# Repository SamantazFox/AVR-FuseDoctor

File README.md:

AVR FuseDoctor
==============

Fuse doctor for AVR-based devices.

Enhanced version froked from https://github.com/nagaokashi/ATTiny_FuseDoctor,
that adds support for ATmegas and ATtiny2313(a)/4313.

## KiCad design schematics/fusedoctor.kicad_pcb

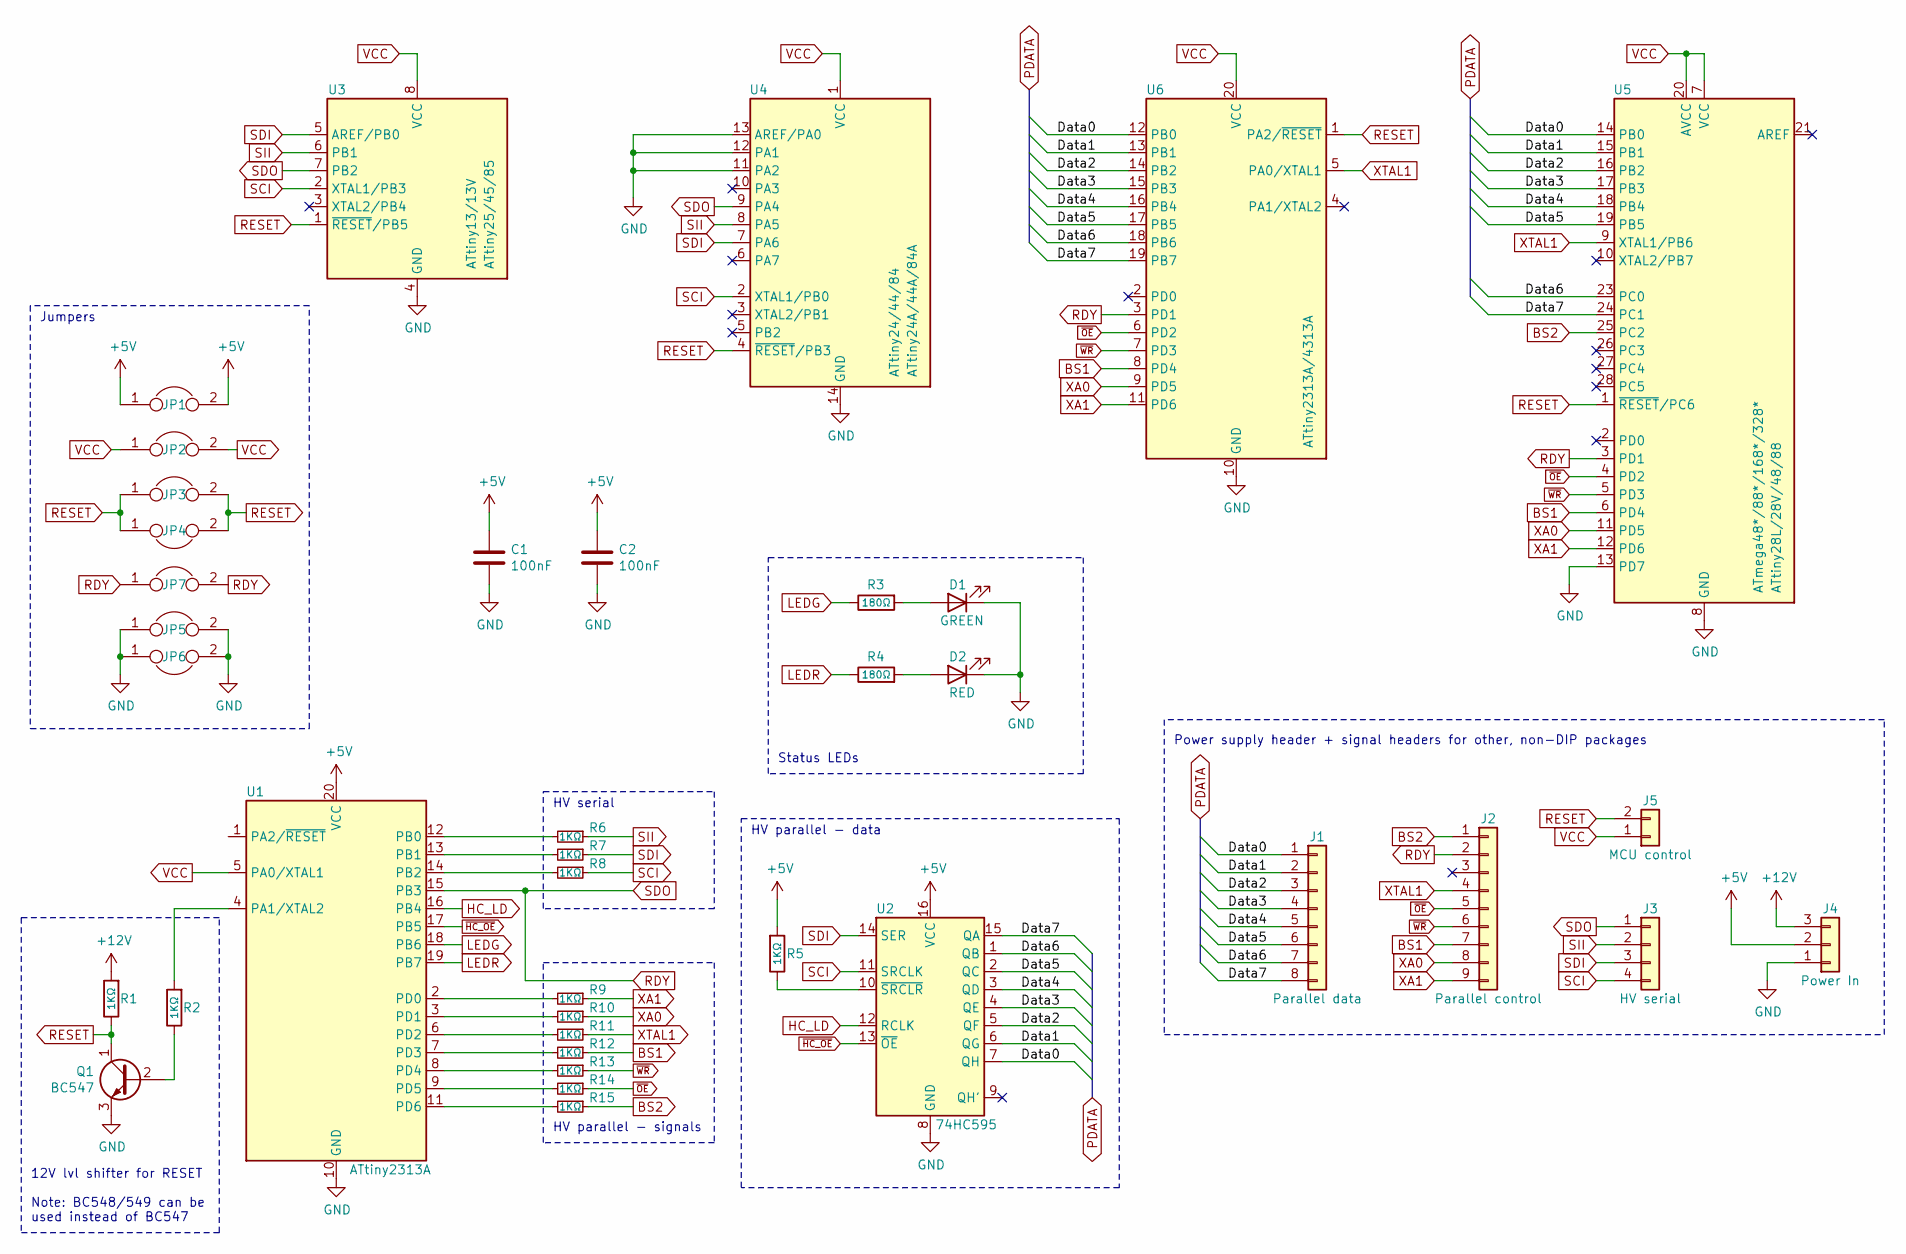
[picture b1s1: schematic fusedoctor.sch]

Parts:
C1, C2: 100nF; C_Axial_L3.8mm_D2.6mm_P7.50mm_Horizontal
D1: GREEN; LED_D3.0mm
D2: RED; LED_D3.0mm
J1: Parallel data; PinHeader_1x08_P2.54mm_Vertical
J2: Parallel control; PinHeader_1x09_P2.54mm_Vertical
J3: HV serial; PinHeader_1x04_P2.54mm_Vertical
J4: Power In; PinHeader_1x03_P2.54mm_Vertical
J5: MCU control; PinHeader_1x02_P2.54mm_Vertical
JP1, JP3, JP4: Jumper; R_Axial_DIN0207_L6.3mm_D2.5mm_P10.16mm_Horizontal
JP2: Jumper; R_Axial_DIN0207_L6.3mm_D2.5mm_P15.24mm_Horizontal
JP5, JP6, JP7: Jumper; R_Axial_DIN0207_L6.3mm_D2.5mm_P7.62mm_Horizontal
Q1: BC547; TO-92
R1, R2, R5, R9, R10, R11, R12, R13, R14, R15: 1KΩ; R_Axial_DIN0207_L6.3mm_D2.5mm_P7.62mm_Horizontal
R3, R4: 180Ω; R_Axial_DIN0207_L6.3mm_D2.5mm_P7.62mm_Horizontal
R6, R7, R8: 1KΩ; R_Axial_DIN0207_L6.3mm_D2.5mm_P10.16mm_Horizontal
U1: ATtiny2313A; DIP-20_W7.62mm_Socket
U2: 74HC595; DIP-16_W7.62mm_Socket
U3: ATtiny13/13V; DIP-8_W7.62mm_Socket
U4: ATtiny24/44/84; DIP-14_W7.62mm_Socket
U5: ATmega48*/88*/168*/328*; DIP-28_W7.62mm_Socket
U6: ATtiny2313A/4313A; DIP-20_W7.62mm_Socket

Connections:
+5V: C1.1, C2.1, J4.2, JP1.1, JP1.2, R5.2, U1.20 (VCC), U2.16 (VCC)
+12V: J4.3, R1.2
/Data0: J1.1, U2.7 (QH), U5.14 (PB0), U6.12 (PB0)
/Data1: J1.2, U2.6 (QG), U5.15 (PB1), U6.13 (PB1)
/Data2: J1.3, U2.5 (QF), U5.16 (PB2), U6.14 (PB2)
/Data3: J1.4, U2.4 (QE), U5.17 (PB3), U6.15 (PB3)
/Data4: J1.5, U2.3 (QD), U5.18 (PB4), U6.16 (PB4)
/Data5: J1.6, U2.2 (QC), U5.19 (PB5), U6.17 (PB5)
/Data6: J1.7, U2.1 (QB), U5.23 (PC0), U6.18 (PB6)
/Data7: J1.8, U2.15 (QA), U5.24 (PC1), U6.19 (PB7)
BS1: J2.7, R12.1, U5.6 (PD4), U6.8 (PD4)
BS2: J2.1, R15.1, U5.25 (PC2)
GND: C1.2, C2.2, D1.1 (K), D2.1 (K), J4.1, JP5.1, JP5.2, JP6.1, JP6.2, Q1.3 (E), U1.10 (GND), U2.8 (GND), U3.4 (GND), U4.11 (PA2), U4.12 (PA1), U4.13 (AREF/PA0), U4.14 (GND), U5.8 (GND), U5.13 (PD7), U5.22 (GND), U6.10 (GND)
HC_LD: U1.16 (PB4), U2.12 (RCLK)
LEDG: R3.1, U1.18 (PB6)
LEDR: R4.1, U1.19 (PB7)
unnamed: D1.2 (A), R3.2
unnamed: D2.2 (A), R4.2
unnamed: Q1.2 (B), R2.1
unnamed: R2.2, U1.4 (PA1/XTAL2)
unnamed: R5.1, U2.10 (~SRCLR)
unnamed: R6.2, U1.12 (PB0)
unnamed: R7.2, U1.13 (PB1)
unnamed: R8.2, U1.14 (PB2)
unnamed: R9.2, U1.2 (PD0)
unnamed: R10.2, U1.3 (PD1)
unnamed: R11.2, U1.6 (PD2)
unnamed: R12.2, U1.7 (PD3)
unnamed: R13.2, U1.8 (PD4)
unnamed: R14.2, U1.9 (PD5)
unnamed: R15.2, U1.11 (PD6)
RDY: J2.2, J3.1, JP7.1, JP7.2, U1.15 (PB3), U3.7 (PB2), U4.9 (PA4), U5.3 (PD1), U6.3 (PD1)
RESET: J5.2, JP3.1, JP3.2, JP4.1, JP4.2, Q1.1 (C), R1.1, U3.1 (~RESET~/PB5), U4.4 (~RESET~/PB3), U5.1 (~RESET~/PC6), U6.1 (PA2/~RESET)
SCI: J3.4, R8.1, U2.11 (SRCLK), U3.2 (XTAL1/PB3), U4.2 (XTAL1/PB0)
SDI: J3.3, R7.1, U2.14 (SER), U3.5 (AREF/PB0), U4.7 (PA6)
SII: J3.2, R6.1, U3.6 (PB1), U4.8 (PA5)
VCC: J5.1, JP2.1, JP2.2, U1.5 (PA0/XTAL1), U3.8 (VCC), U4.1 (VCC), U5.7 (VCC), U5.20 (AVCC), U6.20 (VCC)
XA0: J2.8, R10.1, U5.11 (PD5), U6.9 (PD5)
XA1: J2.9, R9.1, U5.12 (PD6), U6.11 (PD6)
XTAL1: J2.4, R11.1, U5.9 (XTAL1/PB6), U6.5 (PA0/XTAL1)
~HC_OE: U1.17 (PB5), U2.13 (~OE)
~OE: J2.5, R14.1, U5.4 (PD2), U6.6 (PD2)
~WR: J2.6, R13.1, U5.5 (PD3), U6.7 (PD3)

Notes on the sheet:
HV serial
HV parallel - signals
12V lvl shifter for RESET Note: BC548/549 can be used instead of BC547
Status LEDs
HV parallel - data
Power supply header + signal headers for other, non-DIP packages
Jumpers

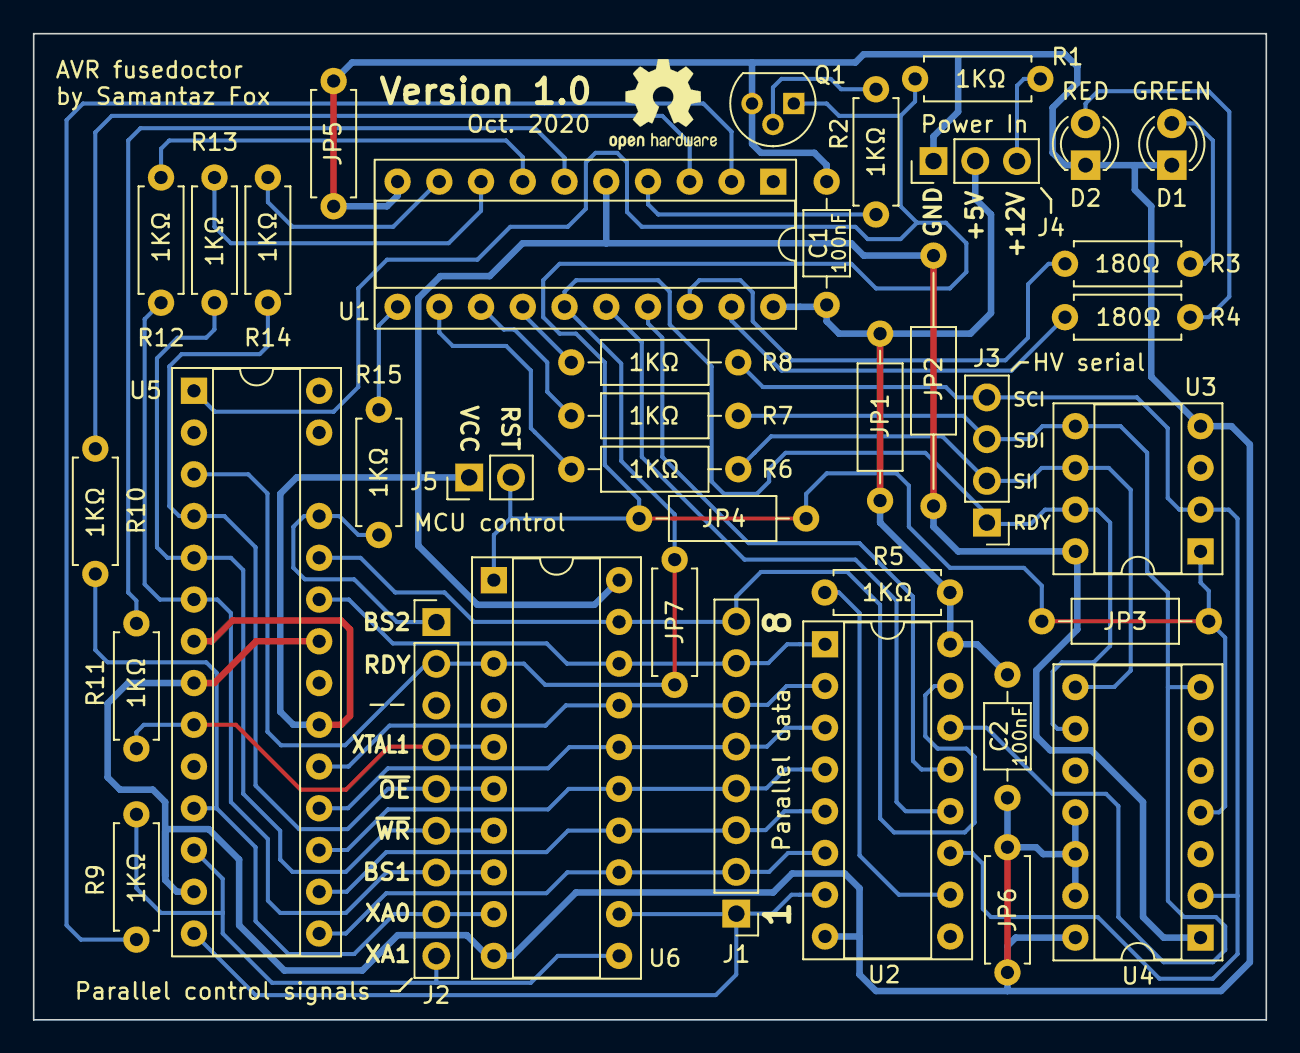
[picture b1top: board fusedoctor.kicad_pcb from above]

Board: 2 copper layers, 75.0 x 60.0 mm, 38 parts (0 on the bottom side), 43 nets.

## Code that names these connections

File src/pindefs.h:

#ifndef __PINDEFS_H__
#define __PINDEFS_H__


/*
 * Common pinouts
*/

// Output to level shifter for !RESET from transistor
#define  PORT_RST      A
#define  PIN_RST       1

// Target VCC
#define  PORT_VCC      A
#define  PIN_VCC       0



/*
 * Pinouts for HV serial programming
*/

// Target Clock Input
#define  PORT_SCI      B
#define  PIN_SCI       2

// Target Data Output
#define  PORT_SDO      B
#define  PIN_SDO       3


// Target Instruction Input
#define  PORT_SII      B
#define  PIN_SII       0

// Target Data Input
#define  PORT_SDI      B
#define  PIN_SDI       1



/*
 * Pinouts for HV parallel programming (control signals)
*/

// Target Clock Input
#define PORT_XTAL1     D
#define PIN_XTAL1      2

// Target Data Output
#define PORT_RDY       B
#define PIN_RDY        3


// Write pulse (active low)
#define PORT_WR        D
#define PIN_WR         4

// Output enable (active low)
#define PORT_OE        D
#define PIN_OE         5

// Byte Select 1
#define PORT_BS1       D
#define PIN_BS1        3

// Byte Select 2
#define PORT_BS2       D
#define PIN_BS2        6

// XTAL Action Bit 0
#define PORT_XA0       D
#define PIN_XA0        1

// XTAL Action Bit 1
#define PORT_XA1       D
#define PIN_XA1        0



/*
 * Pinouts for HV parallel programming (data signals)
*/

// HC595 serial in (data out, same pin as SDI)
#define PORT_HC_DATA   PORT_SDI
#define PIN_HC_DATA    PIN_SDI

// HC595 serial clock (same pin as SCI)
#define PORT_HC_CLK    PORT_SCI
#define PIN_HC_CLK     PIN_SCI

// HC595 "store data" ("shift load"/"RCLK")
#define PORT_HC_LOAD   B
#define PIN_HC_LOAD    4

// HC595 output enable
#define PORT_HC_OE     B
#define PIN_HC_OE      5



/*
 * Pinouts for status LEDS
*/

// Status good/polling LED (Green LED)
#define PORT_LED_G     B
#define PIN_LED_G      6

// Error LED (Red)
#define PORT_LED_R     B
#define PIN_LED_R      7



/*
 * Some macros to emulate Arduino functions
*/

#define LOW  0
#define HIGH 1

#define INPUT  0
#define OUTPUT 1


// Set or clear a register bit
#define sbi(reg, pos) { reg |=  (1 << pos); }
#define cbi(reg, pos) { reg &= ~(1 << pos); }


// digitalWrite()
#define digitalWrite(signal, state) \
	_digitalWrite(PORT_##signal, PIN_##signal, state)

#define  _digitalWrite(port, pin, state)  __digitalWrite(port, pin, state)

#define __digitalWrite(port, pin, state) \
	{ if (state) sbi(PORT##port, pin) else cbi(PORT##port, pin); }


// digitalRead()
#define digitalRead(signal) \
	_digitalRead(PORT_##signal, PIN_##signal)

#define  _digitalRead(port, pin)  __digitalRead(port, pin)

#define __digitalRead(port, pin) ( PIN##port & (1 << pin) )


// pinMode()
#define pinMode(signal, state) \
	_pinMode(PORT_##signal, PIN_##signal, state)

#define  _pinMode(port, pin, state)  __pinMode(port, pin, state)

#define __pinMode(port, pin, state) \
	{ if (state) sbi(DDR##port, pin) else cbi(DDR##port, pin); }



#endif  /* !__PINDEFS_H__ */

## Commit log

2020-10-15 Rename main file
2020-10-16 Code clean-up
2020-10-16 Use standard int types instead of Arduino ones
2020-10-16 Remove code related to the serial port
2020-10-16 Move list of supported devices to a PROGMEM array
    Also add some new devices that will be supported in the future
2020-10-16 Move ATtiny HV serial code to a separate file
2020-10-16 Move source code to a separate folder
2020-10-16 Get rid of Arduino's init/loop functions
2020-10-16 Move 'method_attiny_hvserial' code to a C file
2020-10-16 Use directly avr-gcc for building
2020-10-16 Completely isolate the code related to the 'attiny HV serial' method
    Also add back header, edit the Makefile and adapt the code to make use
    of the known_device_t list.
2020-10-16 Move known_devices code to separate C file, too
2020-11-04 Add board schematics
2020-11-04 Add PCB gerbers
2020-11-04 Add gitignore file
2020-11-04 Update pin definitions to match schematics
2020-11-05 Remove old images
2020-11-05 Add bill of materials (BOM)
2020-11-05 Add ATtiny28L/28V/48/88 and ATmega48/88/168 to the known devices
2020-11-05 Update silkscreen on schematics
2020-11-05 Regenerate back silkscreen gerber
